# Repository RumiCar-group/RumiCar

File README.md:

# RumiCar

> [!IMPORTANT]
> ## 📢 お知らせ / Announcement
>
> **Arduino IDE用のRumiCarライブラリは、Arduino公式のLibrary Managerに登録されました。**
>
> インストール手順（Arduino IDE 内で完結します）:
>
> 1. Arduino IDEのメニューから「スケッチ」→「ライブラリをインクルード」→「ライブラリを管理...」を開く
> 2. 検索ボックスに `RumiCar` と入力
> 3. 表示された `RumiCar` を選び「インストール」をクリック
> 4. 依存ライブラリ（VL53L0X）のインストール確認が表示されたら「Install all」を選択
>
> ライブラリのソースコード（参考）: [RumiCar-group/RumiCar-lib](https://github.com/RumiCar-group/RumiCar-lib)
>
> このリポジトリ内にあった `ArduinoAndESP32/Libraries/` 配下の旧ライブラリ（`.zip` と `RumiCar/` フォルダ）は**削除しました**。古い資料に残る「RumiCar.zip を選択」という手順はもう使えません。上記の Library Manager をご利用ください。
>
> ---
>
> **The RumiCar Arduino library has been published to the Arduino Library Manager.**
>
> Installation steps (all done inside Arduino IDE):
>
> 1. Open **Sketch → Include Library → Manage Libraries...** in Arduino IDE
> 2. Type `RumiCar` in the search box
> 3. Click **Install** on the `RumiCar` entry
> 4. When prompted to install the dependency (VL53L0X), choose **Install all**
>
> Library source code (for reference): [RumiCar-group/RumiCar-lib](https://github.com/RumiCar-group/RumiCar-lib)
>
> The local copy that used to be under `ArduinoAndESP32/Libraries/` **has been removed**. Older materials may still say "select RumiCar.zip" — that procedure no longer works; please use the Library Manager above.

**日本語** | [English (README.en.md)](README.en.md)

コンピュータモジュールの種類によりプログラムや使用コンピュータ言語が異なります。
Arduino Nano と ESP32 の場合はフォルダArduinoAndESP32をお使いください。
Raspberry Pi Zero W の場合はフォルダRasPiをお使いください。Raspiはコンピュータ言語はPythonです。
Raspberry Pi Zero 2 W ＋ カメラの場合は別リポジトリ [RumiCar-Zero2Cam](https://github.com/RumiCar-group/RumiCar-Zero2Cam) をお使いください（SD カードイメージを書き込むだけで走ります。案内は [Zero2Cam](Zero2Cam/README.md) フォルダ）。

画像はYouTubeへのリンクです。クリックしてご覧ください。

- [RumiCar紹介動画](https://youtu.be/DxaY2eCzJzo)
- [衝突回避](https://youtu.be/95pc_4Wf14U)
- [Part 2 of 2 RumiCar on test course](https://youtu.be/oHujTh9AwAw)
- [車載カメラ視点](https://youtu.be/16kOgLMo-Tg)

### 関連リポジトリ（RumiCar ファミリー）

<!-- AUTO-REPOS-JA:START -->
<!-- この表は自動生成です。手で編集しないでください(毎日、公開リポジトリ一覧から再生成されます)。
     説明文・表示順の変更は .github リポジトリの profile/repos-meta.json を編集してください。
     This table is auto-generated daily from the org's public repositories.
     Edit profile/repos-meta.json in the .github repository to change descriptions/order. -->
| リポジトリ | 内容 | ★ |
|---|---|---|
| [**RumiCar**](https://github.com/RumiCar-group/RumiCar) | 本体。サンプルプログラム、ハンズオン教材(PDF)、結線図、開発資料、シミュレータ用プログラム/コース | 35 |
| [**RumiCar-Simulator**](https://github.com/RumiCar-group/RumiCar-Simulator) | ブラウザで動く自動運転シミュレータ(インストール不要・実機互換) | - |
| [**RumiCar-PhotoStrip**](https://github.com/RumiCar-group/RumiCar-PhotoStrip) | 通信量にやさしい写真ストリップ(どのサイトでも使える汎用Web部品・MIT) | - |
| [**RumiCar-VideoLoop**](https://github.com/RumiCar-group/RumiCar-VideoLoop) | 動画ダイジェスト小窓(無音ティーザーをランダム連続再生・クリックで本編へ・MIT) | - |
| [**RumiCarRos**](https://github.com/RumiCar-group/RumiCarRos) | ROS 2対応の実装 | 3 |
| [**RumiCar-Zero2Cam**](https://github.com/RumiCar-group/RumiCar-Zero2Cam) | Raspberry Pi Zero 2 W＋カメラ版。車載プログラム(C++)、PCの走行管理アプリ(C#)、SDカードイメージ(Releasesから入手) | - |
| [**RumiCar-lib**](https://github.com/RumiCar-group/RumiCar-lib) | Arduinoライブラリのソースコード(導入はArduino IDEのライブラリマネージャから。ここからのダウンロードは不要) | - |
| [**RumiCar-AutoPost-Guide**](https://github.com/RumiCar-group/RumiCar-AutoPost-Guide) | Publish a WordPress post; What's New and the Facebook Page update automatically. A bilingual methods guide (ja/en) — setup, pitfalls, and log-based verification. | - |
| [**RumiCar-ReleaseNotes-Guide**](https://github.com/RumiCar-group/RumiCar-ReleaseNotes-Guide) | Publish a GitHub Release, get paired JA/EN WordPress articles automatically — a methods guide with the reference implementation from rumicar.com | - |
| [**RumiCarEX**](https://github.com/RumiCar-group/RumiCarEX) | 関連プロジェクトのfork(派生車体) | - |
| [**micro-airc**](https://github.com/RumiCar-group/micro-airc) | 関連プロジェクトのfork(AI RCカー) | 1 |
| [**rumicar-duck**](https://github.com/RumiCar-group/rumicar-duck) | 関連プロジェクトのfork(アヒル型走行車) | - |
<!-- AUTO-REPOS-JA:END -->

### フォルダの説明

- [**ArduinoAndESP32**](https://github.com/RumiCar-group/RumiCar/tree/master/ArduinoAndESP32)フォルダ<br>RumiCarのコンピュータモジュール(CM)のArduino Nano版とESP32版用のサンプルプルプグラムです。<br>ハンズオンで使用するプログラム（Exercise、Exercise-1.1〜4.2）は、RumiCarライブラリ（v0.5.0以降。Exercise-4 はv0.5.0から）のスケッチ例に入っています。Arduino IDEの「ファイル」→「スケッチ例」→「RumiCar」から開いてください。このフォルダには上級編（Exercise-A2.3など）とサンプルプログラムがあります。RumiCarハンズオン用の資料は[**ハンズオン用テキスト**](https://github.com/RumiCar-group/RumiCar/tree/master/Hands-on%20text)フォルダの下に保存されていますのでまずそちらを参照ください。

  - **Exercise-1 距離を測ってみよう！**<br>RumiCarには車体の前方に3個のレーザー測距モジュールを搭載しています。レーザー測距モジュールは人体に無害のレーザー光線を対象物に当て、その反射光が戻ってくるまでの***時間***を計測することによって距離を測定します。音速はマッハと呼ばれ時速1000km以上の速度ですが、光の速さはその音速の***88万倍***も速いです。その光が反射して返ってくるまでのとても短い時間を計って距離を計測するなんて凄いですね。
  
    - **Exercise-1.1 中央のセンサで測距しよう！**<br>RumiCarに3個搭載されているレーザー測距モジュールのうちの一つ、中央のセンサーを使って距離を測ってみます。Arduino IDEが持っているシリアルモニタの機能を使い、測定した距離を皆さんのパソコンにリアルタイムで表示します。センサの前に手をかざして手を前後に動かすと、手とセンサの間の距離が変わりますのでシリアルモニタに表示される距離の値もリアルタイムで変化します。
    - **Exercise-1.2 3つのセンサで測距だ！**<br>RumiCarに搭載されている3個のセンサを全部同時に動かしてみましょう。左、中央、右のそれぞれのセンサが測定した距離の値を同時にリアルタイムでパソコンの画面に表示します。
    - **Exercise-1.3 シリアルプロッタを使ってみよう**<br>Arduino IDEにはシリアルプロッタの機能もあります。これはデータを自動でグラフ表示してくれる機能です。プログラムはExercise-1.2と同じものを使いますが測定した距離値がリアルタイムに色分けされてグラフ化表示されます。Exercise-1.2と同じようにセンサの前に手をかざしてグラフが変化するか見てみましょう。どの色のグラフがどのセンサの値を表示しているか確かめましょう。このExerciseではExercise-1.2のプログラムをそのまま使いますので専用のプログラムはありません。
  - **Exercise-2 モータ制御**<br>RumiCarはハンドルを曲げる時と走行する時にモータを使います。RumiCarではCMのコンピュータがプログラムに従って、ハンドルを動かしたりRumiCarが走るためにタイヤを回転させたりします。コンピュータモジュールを使ってRumiCarのモータを動かしてみましょう。
    - **Exercise-2.1 ハンドルを切る**<br>RumiCarの前のタイヤを左右に動かしてみましょう。このプログラムではハンドルを左右に切ってそのまま0.5秒保持します。その動作を繰り返します。つまり、左に切って0.5秒、右に切って0.5秒、また左に切って0.5秒と、ずっと繰り返します。
    - **Exercise-2.2 速度制御**<br>RumiCarの走る速度をコントロールしてみましょう。コンピュータモジュールからの命令によって走行用車輪、すなわち後ろのタイヤを回転させます。タイヤの回転速度を変化させることによりRumiCarの走るスピードを変化させることができます。ここではプログラムを使ってタイヤの回転速度を段階的に変化させます。モータの回転音が変わりますのでタイヤの回転を見るのと同時にモータの音の変化にも気をつけてみてください。
    - **Exercise-2.3 前進と後進**<br>実際の自動車は前に進んだり後ろに下がったりします。RumiCarも同様に前進や後進ができます。プログラムを使ってRumiCarを前進させたり後進させてみましょう。RumiCarを走らせる場所が無い時は、RumiCarを手にしっかり持って後ろのタイヤが前進方向に回転したり、後進方向に回転するのを確認しましょう。
    - **Exercise-2.4 ジグザグ走行**<br>RumiCarをジグザグに走行させてみましょう。ハンドルを左右に切りながら前進します。RumiCarを走らせられる場所が無い場合はRumiCarをしっかり手に持って期待通りの動きになっていることを確認しましょう。
  - **Exercise-3 自律走行基礎**<br>自律走行の基礎としてセンサ等が取得した情報を元に判断してRumiCarを制御してみます。前方の障害物や左右の壁などの距離を測定し、停止したり左右にハンドルを切りながらRumiCarを走行させてみます。
    - **Exercise-3.1 安全に停止する車**<br>前方に障害物を発見して安全に停止する車を考えます。RumiCarが直進中に前方に障害物を発見したら停止し、障害物が無くなったら走行そ再開します。障害物が近づいてきたら、安全のために後進します。あなたの手を障害物と仮定してRumiCarがあなたの手にぶつからずに停止するか試してみましょう。RumiCarが停止中にあなたの手をRumiCarに近づけたら安全確保のためにRumiCarが後進しますか？
    - **Exercise-3.2 市街地を走る車**<br>このExerciseでは実際に走行コースを設置してRumiCarを走らせます。左右の壁や前方の障害物を検知しながらRumiCarが走行します。
  - **Exercise-4 AIと一緒にプログラムを改良しよう**<br>やりたいことを日本語で伝えて、AIコーディングエージェント（教材ではGoogleのAntigravity CLI）にスケッチを書き換えてもらいます。方針を考えるのは人、書くのはAI、確かめるのは人。スケッチ例のフォルダにはAIへの約束を書いた`AGENTS.md`が同梱されていて、「名前を付けて保存」すると一緒にコピーされます。解答例（`Exercise-4.1-Answer`、`Exercise-4.2-Answer`）もスケッチ例にあります。
    - **Exercise-4.1 スリップしない前進と後進**<br>Exercise-2.3の発展問題です。「加減速をもう少しスムースにして」のように頼み、AIが書き換えた差分を読んで承認し、実機で確かめます。
    - **Exercise-4.2 はまったら切り返す車**<br>Exercise-3.2の車はカーブで壁に斜めに当たると前後に小刻みに動くだけで抜け出せません。「はまったことをどう知るか」（前後切替の回数、距離が変わらない、三方が近い）と「ハンドルを切り返して脱出する手順」を自分で考えてからAIに頼みます。
- **[ESP32](https://github.com/RumiCar-group/RumiCar/tree/master/ESP32)フォルダ**<br>RumiCarのCMのうち、ESP32はWiFiやBluetoothなどの通信機能を内蔵しています。ここではESP32のBluetooth機能を使ってRumiCarのセンサ測距値を無線で取得して表示させたり、RumiCarをワイヤレスで制御するサンプルプログラムが入っています。
     - **BLEフォルダ**<BR>Bluetooth Low Energy(BLE)での通信。RumiCarのESP32版CMに搭載されているBLEを使ってスマホ(iPhone)と通信してみましょう。3個の測距モジュールでの距離計測値をiPhoneのBLE Scannerとのアプリで表示させています。マルチコネクトが可能なので、個別の機器と接続や切断が不要ですので、一度に複数の機器から1台のRumiCarに接続することができます。展示会などで来場者に各自のスマホからRumiCarに接続してもらい、自分のスマホで計測値を表示させて楽しんでいただくことなどが可能です。
    - **Bluetoothフォルダ**<br>Exercise-1.2はRumiCar ESP32版CM用Bluetoothシリアル通信のサンプルプログラムです。RumiCarをWindows PCとBluetoothで接続してRumiCarのレーザー測距モジュールの測定距離値をパソコンに表示したり、パソコンからコマンドを送ってRumiCarを操作することができます。
      - Windos10とペアリング
      - 設定->デバイス->Bluetoothとその他のデバイス->Bluetoothまたはその他のデバイスを追加する->Bluetooth
      - RumiCar_ESP32を選択
      - デバイスマネージャー->ポート(COMとLPT)で"Bluetooth リンク経由の標準シリアル(COM #)"　を確認する。 #は数字です。　(2個表示される)
      - Arduino IDEの設定でツール->シリアルポート　で、上記COM #に合わせる
      - ESP32が「ケーブルを繋いでいない」のに測距値がシリアルモニタに表示できます。
      - PC側からコマンドを送ってRumiCarをコントロールできます。
      - サンプルプログラムはコマンド「r」、「l」、「f」、「b」に対応しています。それぞれ右、左、前進、後進を0.5秒実行します。コマンドは全て小文字です。 Arduino IDEのシリアルモニタの送信でコマンドを送ります。
      - ケーブル接続が不要なので、走行中に実際の測距データをPC側で取得したり、PC側からコマンドを送ってラジコンのような操作をすることができるようになります。

- **[RasPi](https://github.com/RumiCar-group/RumiCar/tree/master/RasPi)フォルダ**<br>RumiCarのコンピュータモジュールのラズパイ版のライブラリ（RumiCar.py）とサンプルプログラムです。Pythonで記述されています。関数名・値の意味・戻り値はArduino版のライブラリ（RumiCar-lib）と同じで、Exercise-1.1〜3.2の構成もArduino版と揃えています。ラズパイ版CMを使ってRumiCarを動かす場合にお使いください。
  - **Exercise-1 距離を測ってみよう！**
    - **Exercise-1.1 中央のセンサで測距しよう！**
    - **Exercise-1.2 3つのセンサで測距だ！**   
  - **Exercise-2 モータ制御**   
    - **Exercise-2.1 ハンドルを切る**    
    - **Exercise-2.2 速度制御**
    - **Exercise-2.3 前進と後進**
    - **Exercise-2.4 ジグザグ走行**  
   - **Exercise-3 自律走行基礎**
     - **Exercise-3.1 安全に停止する車**   
     - **Exercise-3.2 市街地を走る車**
- **[Zero2Cam](https://github.com/RumiCar-group/RumiCar/tree/master/Zero2Cam)フォルダ**<br>Raspberry Pi Zero 2 W ＋ Camera Module 2 を搭載した RumiCar の案内です。プログラム本体は別リポジトリ [**RumiCar-Zero2Cam**](https://github.com/RumiCar-group/RumiCar-Zero2Cam)（車載は C++、PC の走行管理アプリは C#）にあり、[Releases](https://github.com/RumiCar-group/RumiCar-Zero2Cam/releases) の SD カードイメージを書き込むだけで走ります。PC から状態と車載カメラの画像を見ながら収録し、判断データを改良して車に送れます。配線はラズパイ Zero W 版 CM と同じです。
 - **[ハンズオン用テキスト](https://github.com/RumiCar-group/RumiCar/tree/master/Hands-on%20text)フォルダ**<br>RumiCarのハンズオン用テキスト（テキスト3.1。日本語版と英語版のPDF）が保存されているフォルダです。RumiCarの歴史や仕組み、サンプルプログラムを使ってRumiCarを動作させる方法や例、AIと一緒にプログラムを改良するExercise-4（声でAIに頼む /voice の使い方を含む）が載っています。ハンズオン用テキストはPDF形式で約10MBほどのファイルサイズです。GitHubから直接参照しようとすると表示できないことがあるようです。一旦ダウンロードしていただいてからご覧ください。
- **[教育機関向け追加課題](https://github.com/RumiCar-group/RumiCar/tree/master/%E6%95%99%E8%82%B2%E6%A9%9F%E9%96%A2%E5%90%91%E3%81%91%E8%BF%BD%E5%8A%A0%E8%AA%B2%E9%A1%8C)フォルダ**<br>RumiCarを教材として教育機関にて授業や演習で利用する場合の追加課題です。Rumicarハンズオンの資料はRumiCarの仕組みや構成を学べるように作られています。学生が自ら更に深く考えて課題を克服し、より良いアルゴリズムを開発できるように研究課題の基礎やグループワークに使えるように追加の課題をまとめました。是非ご利用ください。
- **[開発用資料](https://github.com/RumiCar-group/RumiCar/tree/master/%E9%96%8B%E7%99%BA%E7%94%A8%E8%B3%87%E6%96%99)フォルダ**<br>RumiCarの車体やCMを自作する場合の開発用資料です。

  1. RumiCarを自作する場合はまず「RumiCarの作り方」をご覧いただき、RumiCarを作製後、作製したCMとRumiCarが正しく動作できているかの確認のために、「RumiCarの動作確認方法」の内容に従ってご確認ください。是非多くの人たちにオリジナルのRumiCarを作製いただき、RumiCarの世界を楽しんで頂けると嬉しいです<br>1.1 CMの作製においてArduino Nano以外のCM作製のための情報を追加しました。<br>1.2 ステアリングをサーボ化する場合のピンアサイン(13番ピン)を追加しました。
  1. RumiCarを受け取ったり、運送等により故障していないかを確認する場合は「RumiCarの動作確認方法」の内容に従ってRumiCarが正常動作するかご確認ください。
  1. 各CM別のピンアサイン表があります。プログラムの互換性確保のためCMを自作する場合の結線はそれに従ってください。<br>
  - **結線図フォルダ**
    - 結線図(ArduinoNano).jpg<br>RumiCarの基本である、Arduino Nano版CMの結線図です。RumiCarをこれから始める人向け。
    - 結線図(Raspberry Pi Zero W).png<br>ラズパイZero W版CMの結線図です。Pythonを使いたい方、画像認識、AI等挑戦されたい方向け(上級者向け)。
    - 結線図RumiCarG3.1_ESP32.jpg<br>ESP32版CM結線図です。WiFiやBluetooth接続、ニューラルネットワーク(NN)プログラム等に挑戦されたい方向け(上級者向け)。
    - 車体接続結線表.jpg<br>RumiCar車体側の結線図です。車体を自作されたい方は、このインターフェイスに合わせて作製ください。
    - ピンアサインArduino-ESP32-RasPi-Obniz<br>Rumicar車体のインターフェイスと、各CMのArduino nano、ESP32、ラズパイ、Obnizのピンアサインを一つの表にまとめたものです。
  - **RumiCarの作り方**<br>RumiCar車体の開発方法や各種CMの作製方法が掲載されています。RumiCarの自作を考えられている方は、この資料を参考に是非オリジナルのRumiCarを作製してみてください。作製したRumiCarは「RumiCarの動作確認方法.pdf」の内容に従って動作確認ができます。   
  - **RumiCarの動作確認方法**<br>RumiCarを新規に作製した場合や、運送などにより故障が発生していないか、のためにRumiCarが正常に動作するか確認するための手順をまとめた資料です。こちらを参考にRumiCarの動作確認をしましょう。

- **RumiCar Simulator(ブラウザ版シミュレータ)**<br>ブラウザ上で RumiCar の走行プログラムを書いて試せるシミュレータです → [**RumiCar Simulator**](https://www.rumicar.com/simulator/)。実機が無くてもプログラムの動作を確認でき、車種(FF/FR/4WD × ノーマル/ドリフト)ごとの挙動の違いも体験できます。ここで作った Arduino C++ のプログラムは**そのまま実機 RumiCar でも動作**します。ソースコードは [**RumiCar-group/RumiCar-Simulator**](https://github.com/RumiCar-group/RumiCar-Simulator) で公開しています(自分のサーバーで動かす手順も同梱)。
  - **[programs](https://github.com/RumiCar-group/RumiCar/tree/master/programs)フォルダ**<br>シミュレータ用の走行プログラム集です。車種別に最適化した「Fable Racing Line」6種と、その**設計思想・各定数の意味・実車でのチューニング手順**を [programs/README.md](https://github.com/RumiCar-group/RumiCar/tree/master/programs) に解説しています(各 .ino の冒頭にも「なぜこの設定にしたか」を記載)。利用者が改変したプログラムは [programs/community](https://github.com/RumiCar-group/RumiCar/tree/master/programs/community) に別名で投稿でき(プルリクエスト方式)、シミュレータの「🌐 みんなの投稿」から誰でも再利用できます。
  - **[courses](https://github.com/RumiCar-group/RumiCar/tree/master/courses)フォルダ**<br>シミュレータ用のコースデータです。30種のテストコースと、利用者が投稿したコース([courses/community](https://github.com/RumiCar-group/RumiCar/tree/master/courses/community))が入っています。投稿方法は [courses/README.md](https://github.com/RumiCar-group/RumiCar/tree/master/courses) を参照してください。

### ハードウェア構成

RumiCar 車体は、車体前部に **3 基のレーザー測距（ToF）モジュール**（左・中央・右）を搭載し、その測定値をコンピュータモジュール（CM）が処理して、ステアリングと走行モータを制御します。CM は USB ケーブルで PC に接続してプログラムを書き込みます。

CM は用途に応じて複数の選択肢があります。

| CM | 言語 | 主な用途 |
|---|---|---|
| **Arduino Nano** | C++ | 基本構成。これから始める方向け |
| **ESP32** | C++ | Wi-Fi / Bluetooth・BLE 連携、ニューラルネットワーク等（上級者向け） |
| **Raspberry Pi Zero W** | Python | 画像認識・AI 等（上級者向け） |
| **Raspberry Pi Zero 2 W ＋ カメラ** | C++（車載）／C#（PC） | カメラ画像を PC に送って収録し、判断データを改良する自動運転。SD カードイメージで配布 → [RumiCar-Zero2Cam](https://github.com/RumiCar-group/RumiCar-Zero2Cam)（配線は Zero W 版と同じ） |
| **Obniz** | — | ピンアサイン表に対応表を掲載 |

結線図・ピンアサイン表・「RumiCar の作り方」「RumiCar の動作確認方法」は、上の「フォルダの説明」にある[開発用資料フォルダ](https://github.com/RumiCar-group/RumiCar/tree/master/%E9%96%8B%E7%99%BA%E7%94%A8%E8%B3%87%E6%96%99)にあります。自作される場合は、プログラムの互換性確保のため、ピンアサイン表に従って結線してください。

### 参加する（協力者募集）

RumiCar は有志で開発しています。**一緒に RumiCar したい方・企業を募集しています。**

- ソフトウェア（自動運転アルゴリズム、IDE、画像認識、Autoware 導入）
- ハードウェア（車体開発・量産、CM 開発、PCB 設計）
- Website 編集・管理（WordPress）、技術アドバイザー
- 広報（YouTube 動画編集、イベント告知）、イベント運営、資金調達

貢献可能な分野とモチベーションを添えて **info@RumiCar.com** までご連絡ください。各国での開発・教室・トレーニング・カンファレンス開催も計画しており、各国拠点でご協力いただける方を探しています。

  ### その他大事なこと
  - [**RumiCar website**](https://www.rumicar.com)<br>RumiCarのwebisteです。今後このwebisteを発展させたいので、websiteの編集をしてくださる方は是非ご連絡ください!
  - [**RumiCar YouTube**](https://www.youtube.com/channel/UCVg3CBSVBcc_00FdC6q2wDg)<br>RumiCarのYouTubeチャンネルです。RumiCarの紹介動画や各種走行動画、開発途中の各種テストの動画などがアップロードされています。是非チャンネル登録をお願いします。また、動画編集をしてくださる方も是非ご連絡ください。
  - [**RumiCar group**](https://www.facebook.com/groups/rumicar)<br>RumiCarのFaceBookグループです。皆様のご参加をお待ちしてます。
  - [**connpass**](https://rumicar.connpass.com)<br>RumiCarの走行会や開発教室、オンラインセミナーなどイベント告知や参加者募集のページです。RumiCarイベントに参加ご希望の方は是非メンバー登録をお願いいたします。
  - [**RumiCarハンズオン中継の録画**](https://youtu.be/99zH73B8NUo)<br>ALGYANとコラボしたRumiCarイベントのアーカイブです。イベント内でExerciseの解説やデモをしています。

Issue・プルリクエストは**英語でも日本語でも歓迎**します。 / Issues and pull requests are welcome in English or Japanese.

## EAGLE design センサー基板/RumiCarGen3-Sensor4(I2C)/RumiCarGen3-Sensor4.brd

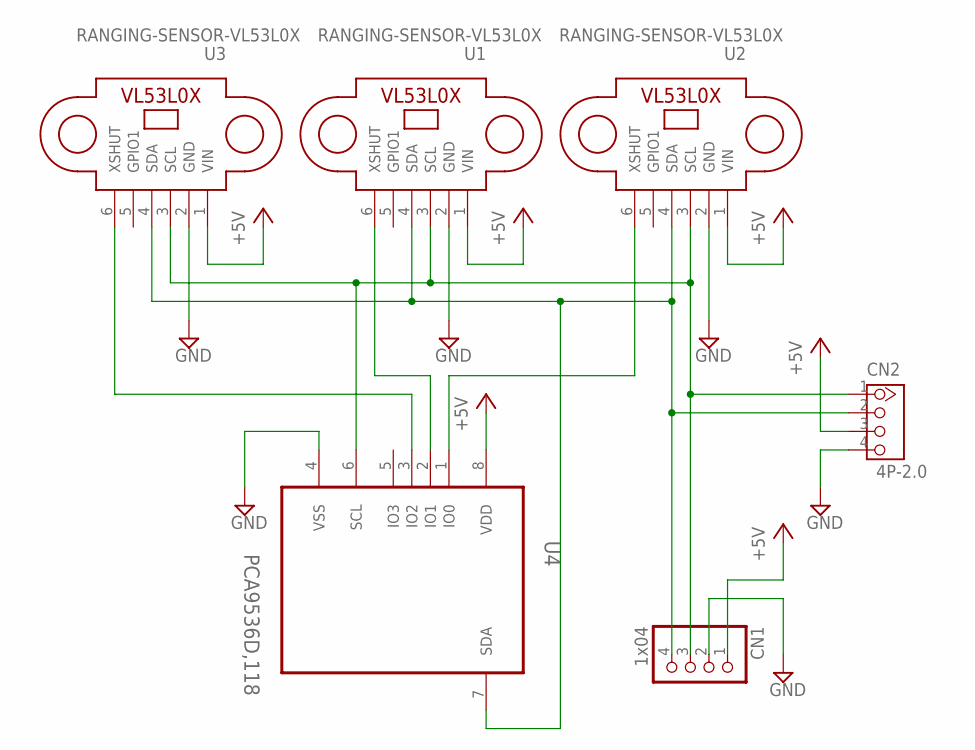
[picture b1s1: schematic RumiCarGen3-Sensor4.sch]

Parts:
CN1: 1x04; 1X04
CN2: 4P-2.0; HW4-2.0
U1, U2, U3: RANGING-SENSOR-VL53L0X
U4: PCA9536D,118; SOIC127P600X175-8N

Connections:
+5V: CN1.1, CN2.3, U1.1 (VIN), U2.1 (VIN), U3.1 (VIN), U4.8 (VDD)
GND: CN1.2, CN2.4, U1.2 (GND), U2.2 (GND), U3.2 (GND), U4.4 (VSS)
unnamed: U1.6 (XSHUT), U4.2 (IO1)
unnamed: U2.6 (XSHUT), U4.1 (IO0)
unnamed: U3.6 (XSHUT), U4.3 (IO2)
unnamed: CN1.3, CN2.1, U1.3 (SCL), U2.3 (SCL), U3.3 (SCL), U4.6 (SCL)
unnamed: CN1.4, CN2.2, U1.4 (SDA), U2.4 (SDA), U3.4 (SDA), U4.7 (SDA)

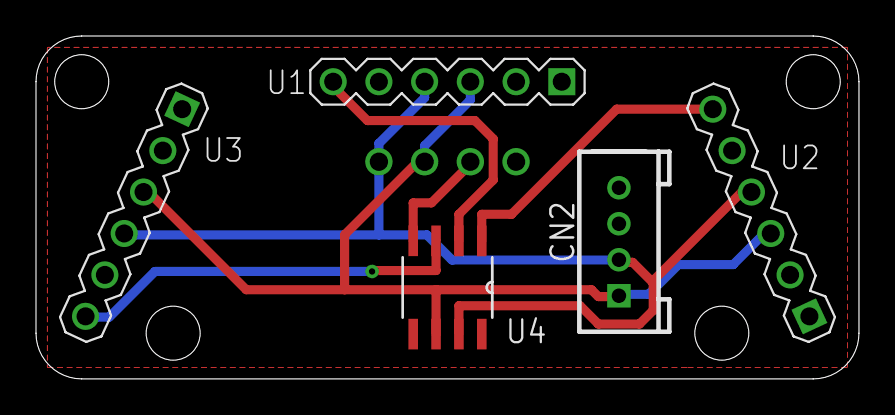
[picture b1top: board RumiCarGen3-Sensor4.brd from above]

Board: 2 copper layers, 45.7 x 19.1 mm, 6 parts (1 on the bottom side), 7 nets.

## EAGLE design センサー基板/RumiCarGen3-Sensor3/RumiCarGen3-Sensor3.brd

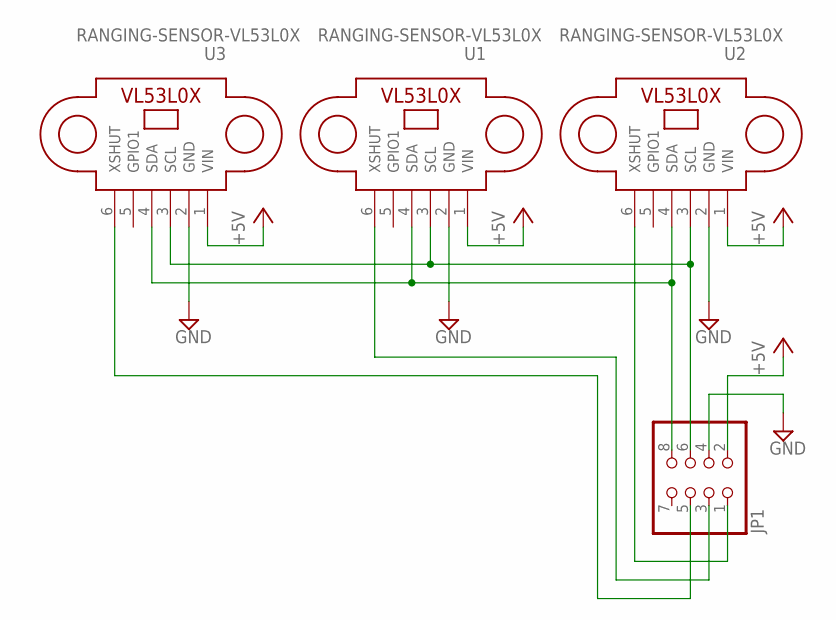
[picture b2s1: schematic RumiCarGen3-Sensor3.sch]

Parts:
JP1: PINHD-2X4; 2X04
U1, U2, U3: RANGING-SENSOR-VL53L0X

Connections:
+5V: JP1.2, U1.1 (VIN), U2.1 (VIN), U3.1 (VIN)
GND: JP1.4, U1.2 (GND), U2.2 (GND), U3.2 (GND)
unnamed: JP1.1, U2.6 (XSHUT)
unnamed: JP1.3, U1.6 (XSHUT)
unnamed: JP1.5, U3.6 (XSHUT)
unnamed: JP1.6, U1.3 (SCL), U2.3 (SCL), U3.3 (SCL)
unnamed: JP1.8, U1.4 (SDA), U2.4 (SDA), U3.4 (SDA)

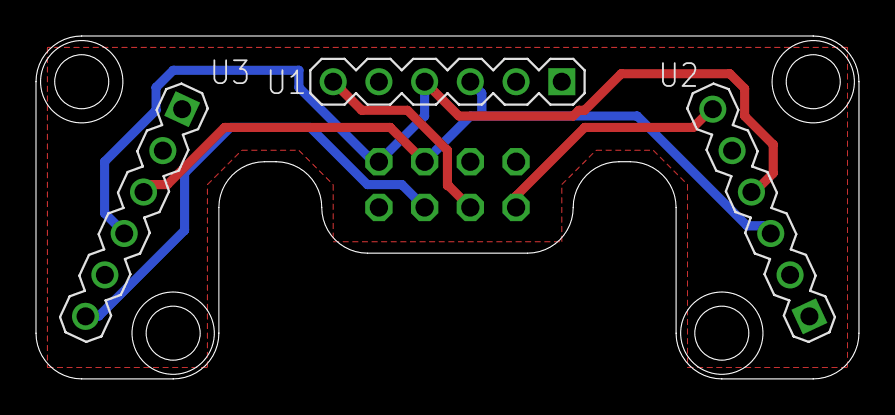
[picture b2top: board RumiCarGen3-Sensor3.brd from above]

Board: 2 copper layers, 45.7 x 19.1 mm, 4 parts (1 on the bottom side), 7 nets.

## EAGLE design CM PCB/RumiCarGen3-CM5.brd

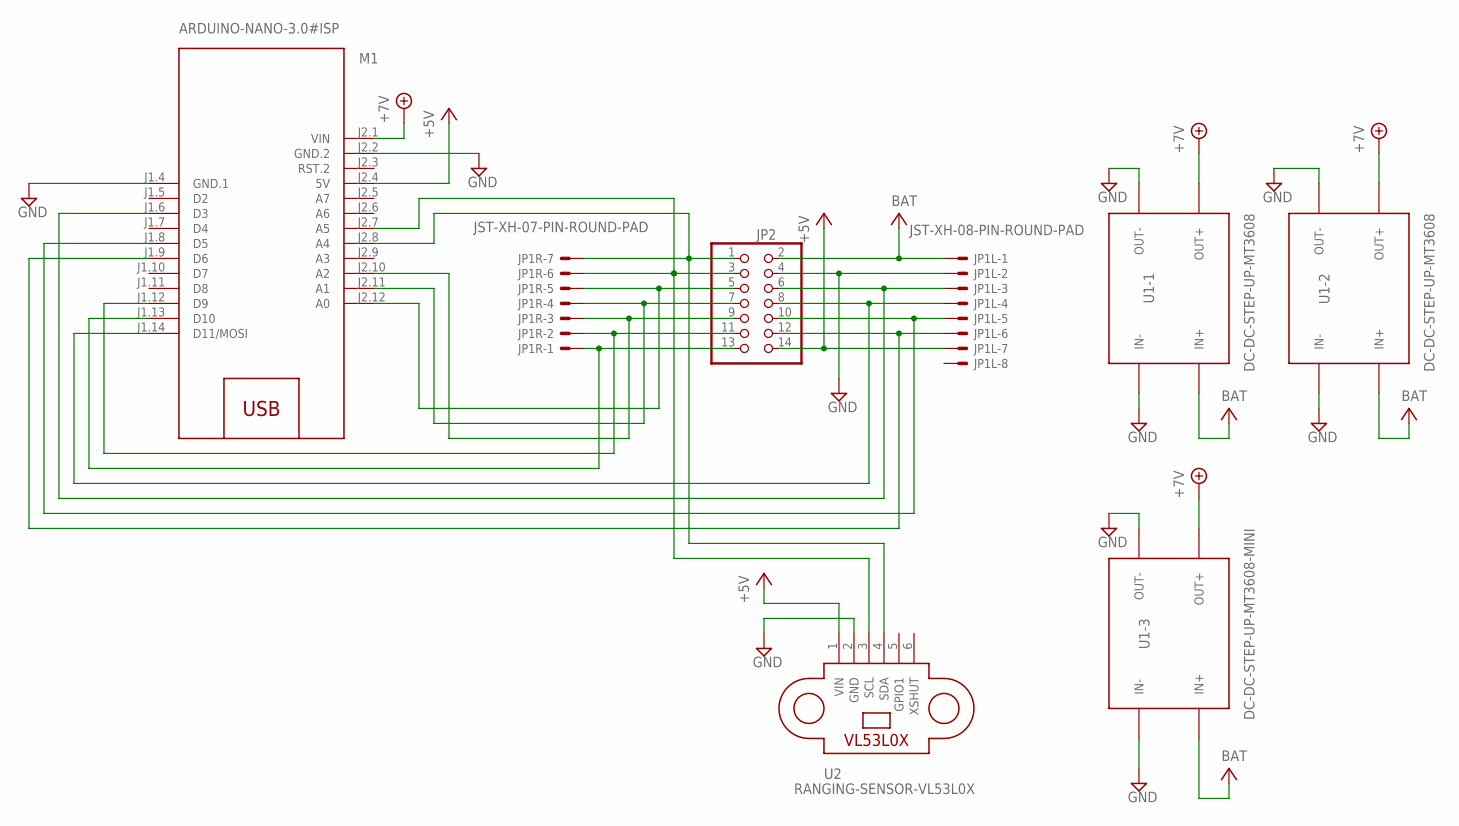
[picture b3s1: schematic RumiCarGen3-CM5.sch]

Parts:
JP1L: JST-XH-08-PIN-ROUND-PAD; JST-XH-08-PACKAGE-ROUND-PAD
JP1R: JST-XH-07-PIN-ROUND-PAD; JST-XH-07-PACKAGE-ROUND-PAD
JP2: PINHD-2X7; 2X07
M1: ARDUINO-NANO-3.0#ISP
U1-1, U1-2: DC-DC-STEP-UP-MT3608
U1-3: DC-DC-STEP-UP-MT3608-MINI
U2: RANGING-SENSOR-VL53L0X

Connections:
+5V: JP1L.7, JP2.14, M1.J2.4 (5V), U2.1 (VIN)
+7V: M1.J2.1 (VIN), U1-1.OUT+, U1-2.OUT+, U1-3.OUT+
GND: JP1L.2, JP2.4, M1.J1.4 (GND.1), M1.J2.2 (GND.2), U1-1.IN-, U1-1.OUT-, U1-2.IN-, U1-2.OUT-, U1-3.IN-, U1-3.OUT-, U2.2 (GND)
unnamed: JP1L.6, JP2.12, M1.J1.9 (D6)
unnamed: JP1L.5, JP2.10, M1.J1.8 (D5)
unnamed: JP1L.3, JP2.6, M1.J1.6 (D3)
unnamed: JP1L.4, JP2.8, M1.J1.14 (D11/MOSI)
unnamed: JP1R.1, JP2.13, M1.J1.13 (D10)
unnamed: JP1R.2, JP2.11, M1.J1.12 (D9)
unnamed: JP1R.3, JP2.9, M1.J2.10 (A2)
unnamed: JP1R.4, JP2.7, M1.J2.11 (A1)
unnamed: JP1R.5, JP2.5, M1.J2.12 (A0)
unnamed: JP1R.7, JP2.1, M1.J2.8 (A4), U2.4 (SDA)
unnamed: JP1R.6, JP2.3, M1.J2.7 (A5), U2.3 (SCL)
V+: JP1L.1, JP2.2, U1-1.IN+, U1-2.IN+, U1-3.IN+

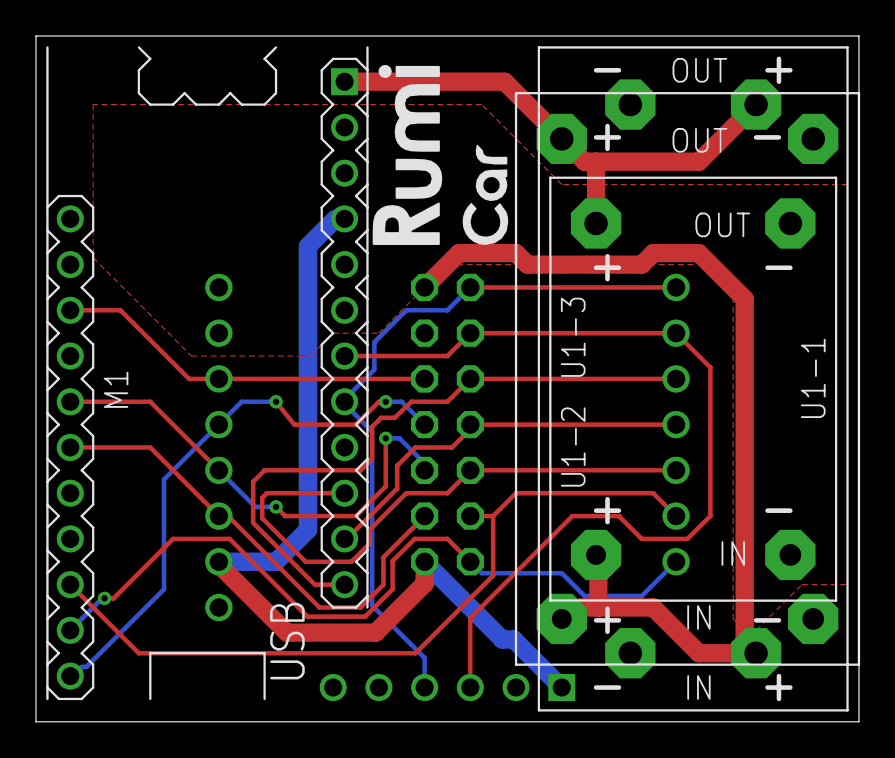
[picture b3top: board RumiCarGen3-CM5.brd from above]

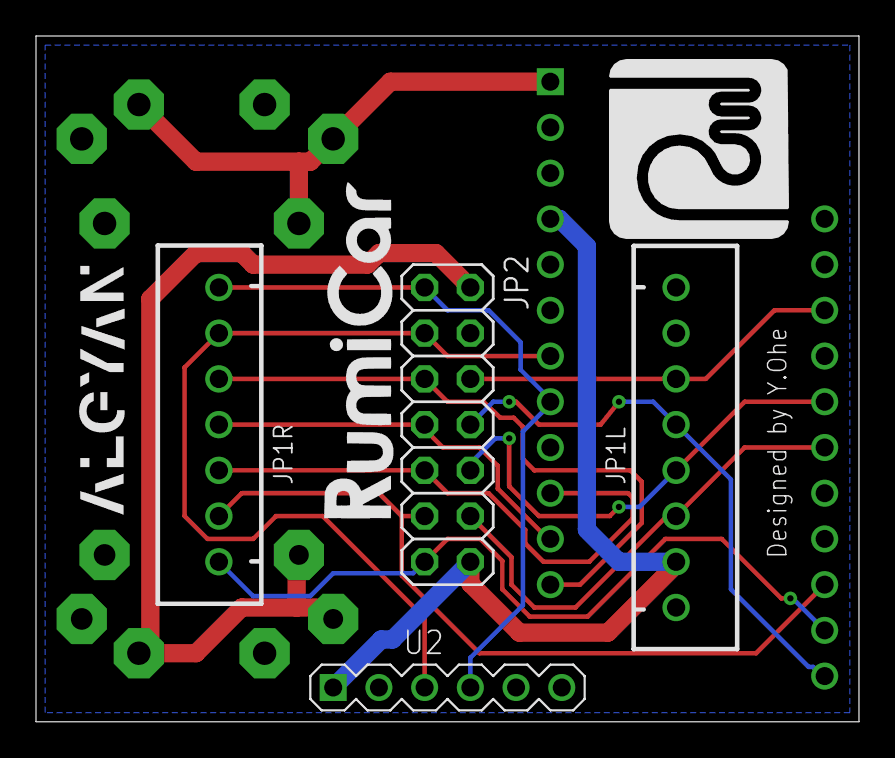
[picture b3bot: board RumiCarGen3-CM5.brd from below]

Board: 2 copper layers, 45.7 x 38.1 mm, 8 parts (4 on the bottom side), 15 nets.

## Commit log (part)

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2020-12-24 Create センサー基板
2020-12-24 Create I2C化
2021-01-05 Create 20210110 イベントevent
2021-01-13 Create Readme English
2021-01-13 Update Readme English
2021-01-13 Rename Readme English to Readme English.md
2021-03-13 Create aa
2021-12-12 Create Event slides
2022-07-31 Create CM PCB
2022-07-31 Create file
2022-08-12 fix function name
2022-08-12 fix 3 sensors output
2022-08-12 use .so file from the repo
2022-08-12 add documentation for RasPi
2022-08-12 improve camera example a bit
2023-01-29 README: cleanup and video streaming instruction
2023-01-30 RasPi README revert to 1 column
2023-03-25 Add files via upload
    本日の資料です。
2023-03-25 Add files via upload
    2023年3月25日sonyイベント用ハンズオンテキスト
2023-05-26 Create Troubleshooting
2023-12-24 CM PCB data added.
2024-02-17 Add Gen3-Sensor3 PCB data.
2024-02-18 Add Gen3-Sensor4(I2C) PCB data.
2024-03-17 Create SPRESENSE
2024-03-29 Create Arduino Nano with various DCDC converter
2024-03-29 Create test
2024-03-29 Rename CM PCB/RumiCarGen3-CM5.brd to CM PCB/Ohe大栄 san CM/RumiCarGen3-CM5.brd
2024-03-29 Rename CM PCB/RumiCarGen3-CM5.pdf to CM PCB/Ohe大栄 san CM/RumiCarGen3-CM5.pdf
2024-03-29 Rename CM PCB/RumiCarGen3-CM5.sch to CM PCB/Ohe大栄 san CM/RumiCarGen3-CM5.sch
2024-03-29 Rename CM PCB/RumiCarGen3-CM5_2020-05-22.zip to CM PCB/Ohe大栄 san CM/RumiCarGen3-CM5_2020-05-22.zip
2024-03-29 Create Arduino Nano CM with various DCDC converters
2024-04-18 Update streaming information
2024-04-27 add codeowners
2024-06-22 Create RumiCar接続関係(第三世代)
2024-07-03 Support Spresense and fix return type mismatch bug.
2024-08-11 Create RumiCar NIIGATA
2024-08-11 Update RumiCar NIIGATA
2024-10-19 Create a
2024-12-19 Rename 開発用資料/結線図RasPiPICO.jpg to 開発用資料/結線図/RasPiPICO.jpg
2025-01-10 RasPi Pico
2025-06-22 Rename Front_StearParts_for_offroad.step to Front axle parts/Front_StearParts_for_offroad.step
2025-07-18 Rename README.MD to README.MD
2025-07-18 Rename RumiCar Hands-on English(20210110 ver).pdf to RumiCar Hands-on English(20210110 ver).pdf
2025-07-18 Rename RumiCarハンズオン(20210110編).pdf to RumiCarハンズオン(20210110編).pdf
2025-07-18 Rename RumiCarハンズオン(20230325編)202230324.pdf to Hands-on text/RumiCarハンズオン(20230325編)202230324.pdf
2025-07-22 Rename RumiCar Hands-on English(202507121ver)CCHver.pdf to RumiCar Hands-on English(20250721ver)CCHver.pdf
2025-10-19 feat: git action release
2025-10-21 feat: update the release readme
2026-01-19 Rename CM PCB/Kataoka san CM/RasPiPICO.png to CM PCB/Kataoka san CM/RasPi/RasPiPICO.png
2026-01-19 Rename CM PCB/Kataoka san CM/結線図RasPiPICO.jpg to CM PCB/Kataoka san CM/RasPi/結線図RasPiPICO.jpg
2026-01-19 Rename CM PCB/Kataoka san CM/Spresense_CM.pdf to CM PCB/Kataoka san CM/SPRESENSE/Spresense_CM.pdf
2026-01-19 Rename 開発用資料/RumiCar接続関係(第三世代)20260117.docx to 開発用資料/RumiCar接続関係(第三世代)/RumiCar接続関係(第三世代)20260117.docx
2026-05-03 Update README with library manager announcement
    Added announcement about RumiCar library availability in Arduino Library Manager and future removal of old libraries.
2026-05-03 Revise README for RumiCar Library installation instructions
    Updated README to reflect the RumiCar library's registration in the Arduino Library Manager and recommended installation method.
2026-05-03 Deprecate local RumiCar library with warning
    Added a deprecation warning for the local RumiCar library.
2026-05-03 Rename .github/README.md to WORKFLOWS.md to avoid overriding repository top-level README
    GitHub displays .github/README.md in preference over the repository root README.md. Renaming this internal Workflows documentation file so the main RumiCar README is correctly shown on the repository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
2026-05-03 Clarify install steps and reposition library repo link
    Restructures the library installation announcement to reduce learner confusion.
    Problem: The previous wording placed the RumiCar-lib repository link inline with the install instructions, which could lead learners to navigate there instead of completing the install entirely withi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
    Changes (both Japanese and English):
    - Added an explicit heading 'Installation steps (all done inside Arduino IDE)' to make it clear the entire process happens in the IDE
    - Replaced the single inline paragraph with a numbered 4-step procedure
    - Added step 4 covering the VL53L0X 'Install all' dependency prompt
2026-05-03 Clarify install steps in Libraries/README.md
    Applies the same install-instruction improvements as the top-level README (commit 2187288) to ArduinoAndESP32/Libraries/README.md, so the messaging is consistent regardless of which README a learner 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
    Changes (both Japanese and English Important callout):
    - Added an explicit heading 'Installation steps (all done inside Arduino IDE)' to make clear the entire process happens in the IDE
    - Replaced the single inline paragraph with a numbered 4-step procedure
    - Added step 4 covering the VL53L0X 'Install all' dependency prompt
    - Moved the RumiCar-lib repository link to its own line, labeled 'Library source code (for reference)' to p

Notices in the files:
parts and their libraries:
diy-modules: Released under the Creative Commons Attribution 4.0 International License: http://creativecommons.org/licenses/by/4.0
